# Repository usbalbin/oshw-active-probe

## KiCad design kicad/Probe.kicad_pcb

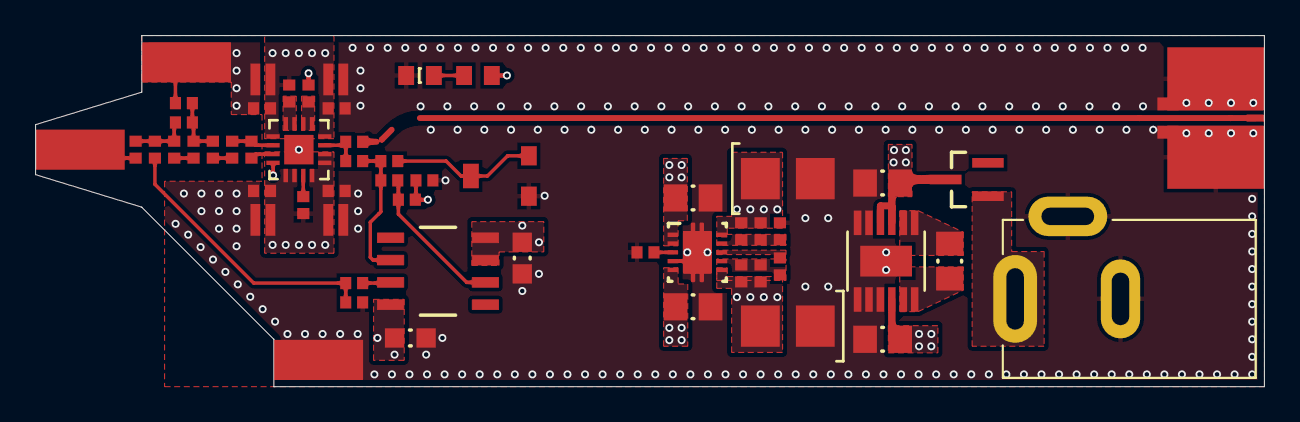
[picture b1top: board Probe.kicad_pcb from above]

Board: 4 copper layers, 70.0 x 20.0 mm, 57 parts (0 on the bottom side), 31 nets.

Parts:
C1: 330p; CAPC0402(1005)50_M
C2: 47p; CAPC0402(1005)50_M
C3: 100p; CAPC0402(1005)50_M
C4: 1.1p; CAPC0402(1005)50_M
C5: 1.3p; CAPC0402(1005)50_M
C6, C8, C9, C18, C19, C20, C21: 10n; CAPC0402(1005)50_M
C7: 1u; CAPC0805(2012)145_M
C10, C11: 22u; KEMET B_M
C12, C13: 100n; CAPC0603(1608)100_M
C14, C15, C16, C17: 100n LICC; CAPC0306_M
C22, C23, C24, C25: 4.7u; CAPC0805(2012)100_M
D1: BAT54; INF-PG-SC59_M
D2: VLMTG1300-GS08; LED0603(1608)_M
J1, J2, J5: 0339-0-15-01-15-27-10-0; MILL-MAX 0339
J3: 901-10511-3
J4: 2.1/5.5mm; CUI PJ-002A
R1: 100; RESC0402(1005)_M
R2: 0; RESC0402(1005)_M
R3: 1.60M; RESC0402(1005)_M
R4: 422K; RESC0402(1005)_M
R6: 1.91M; RESC0402(1005)_M
R8: 66.5k; RESC0402(1005)_M
R9: 68; RESC0402(1005)_M
R10: 10.0M; RESC0402(1005)_M
R11: 51.0K; RESC0402(1005)_M
R12: 10.0K; RESC0402(1005)_M
R13: 1k; PVG3A
R15: 5.60K; RESC0402(1005)_M
R16: 17.8k; RESC0402(1005)_M
R17, R18: 1.00K; RESC0402(1005)_M
R19: 49.9; RESC0402(1005)_M
R20: 41.2k; RESC0402(1005)_M
R21: 91.0K; RESC0402(1005)_M
R22: 10.2k; RESC0402(1005)_M
R23: 18.0K; RESC0402(1005)_M
R24: 4.70K; RESC0603(1608)_M
U1: BUF802; VQFN16_RGT_TEX- OSHPARK
U2: OPA140; SOIC-8
U3: TPS7A39; DSC0010J_NV
U4: LTC3261; MSOP-12_MSE

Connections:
GND: C3.2, C9.2, C10.2, C11.1, C12.2, C13.1, C14.2, C15.1, C16.2, C17.1, C18.2, C19.1, C20.2, C21.1, C22.2, C23.1, C24.2, C25.2, D2.2, J2.1, J3.2, J4.2, J4.3, J5.1, R4.2, R8.2, R13.3, R22.2, U1.17, U3.4, U3.11, U4.1, U4.2, U4.3, U4.11, U4.12, U4.EPAD
NetC1_1: C1.1, C5.2, R3.2, R4.1
NetC1_2: C1.2, R2.1
NetC2_1: C2.1, R11.1, R12.1, U2.2
NetC2_2: C2.2, R15.2, U2.6
NetC3_1: C3.1, R15.1, U1.4
NetC4_1: C4.1, R1.2, R3.1, R6.1
NetC4_2: C4.2, C5.1
NetC6_1: C6.1, R20.2, R22.1, U3.9
NetC7_1: C7.1, U4.7, U4.8
NetC7_2: C7.2, U4.5, U4.6
NetC8_1: C8.1, R21.1, R23.1, U3.7
NetC9_1: C9.1, U3.3
NetD1_1: D1.1, J4.1
NetD2_1: D2.1, R24.2
NetR2_2: R2.2, R10.1, U1.2
NetR6_2: R6.2, R8.1, R9.1
NetR9_2: R9.2, U2.3
NetR10_2: R10.2, U1.3
NetR11_2: R11.2, R19.1, U1.11
NetR12_2: R12.2, R13.1, R13.2
NetR16_1: R16.1, U1.7
NetR17_1: R17.1, U1.15, U1.16
NetR18_1: R18.1, U1.13, U1.14
NetR23_2: R23.2, U3.8
OUT: J3.1, R19.2
TIP: J1.1, R1.1
V+: C22.1, C24.1, D1.3, U3.1, U3.2, U4.9, U4.10
V-: C23.2, C25.1, U3.5, U4.4
VCC: C6.2, C10.1, C12.1, C14.1, C16.1, C18.1, C20.1, R17.2, R20.1, R24.1, U1.1, U1.12, U2.7, U2.8, U3.10
VEE: C8.2, C11.2, C13.2, C15.2, C17.2, C19.2, C21.2, R16.2, R18.2, R21.2, U1.5, U1.6, U1.8, U1.9, U1.10, U2.4, U3.6

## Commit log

2025-11-09 Convert to kicad - should probably very gerbers especially the exposed metal of the 50 ohm output
2025-11-09 Fix exposed metal of the 50 ohm output. Still have to fix so we can pour copper
2025-11-10 Add missing sheets
